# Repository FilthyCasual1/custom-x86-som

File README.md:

# Custom x86 SOM — placement handoff

Open `hardware/x86-som-preliminary.kicad_pro` in KiCad 10. The matching schematic has 18 sheets; the matching PCB contains 96 staged components and zero routed tracks. Project-local symbol and footprint libraries are included. Move components in the PCB editor to start exploring placement; no board outline has been chosen.

**This is an incomplete preliminary design, not fabrication-ready.** See `hardware/LIBRARY-STATUS.md` for the current verification matrix. The CPU socket and Q370 still use padless placement envelopes. Other packages include source-checked geometry and explicitly marked provisional choices. Electrical and assembly validation remains incomplete.

The full library is `hardware/SOM_Full.kicad_sym`; use `hardware/parts-catalog.json` for part numbers. CPU socket: Foxconn PE115127-4041-01H. DDR4 sockets: TE2309407-1. The full pin inventories have1151 CPU contacts,874 PCH balls and456 BMC balls.

## Files

- `hardware/x86-som-preliminary.kicad_sch`: source-based schematic draft.
- `hardware/x86-som-preliminary.kicad_pcb`: component staging board with nets assigned to available pads.
- `hardware/SOM.kicad_sym`, `hardware/SOM.pretty/`: portable project libraries.
- `hardware/footprint-status.json`: footprint provenance and provisional status.
- `hardware/placement-validation.json`: component count and schematic nodes without pads.
- `hardware/open-items.md`: next engineering checks.
- `output/pdf/x86-som-preliminary.pdf`: schematic preview.
- `docs/reference/`, `docs/manifest.json`: downloaded documents and source inventory.
- `research/conversation-source.json`: recovered original specification conversation.

KiCad successfully exported the schematic and reloaded the 96-component PCB. ERC reports 102 errors and 349 warnings; see `hardware/erc.rpt`. These remain unresolved, and no routing, signal-integrity, power-integrity, boot or fabrication validation has been claimed.

The source specification is ChatGPT conversation “Compact SOM Motherboard Design”, ID `6ab03890-806c-83ea-97a4-768561390f3c`. Prior assistant claims are research leads. The earlier claimed downloadable engineering packs were not recovered. Actual donor schematics and manufacturer documents have been downloaded separately.

Generation scripts are development tools. **Do not rerun them after manual KiCad edits:** they overwrite schematic/PCB files and regenerate symbol UUIDs.

## Public repository contents

This public snapshot contains the KiCad files, libraries, generation scripts, engineering notes and previews from local commit `4b89cf6`. The original conversation archive and downloaded third-party reference documents/text extracts remain local; paths to those files describe the local research workspace. `docs/manifest.json` records the source inventory. Some generators require those local source files and will not run from this public checkout alone.

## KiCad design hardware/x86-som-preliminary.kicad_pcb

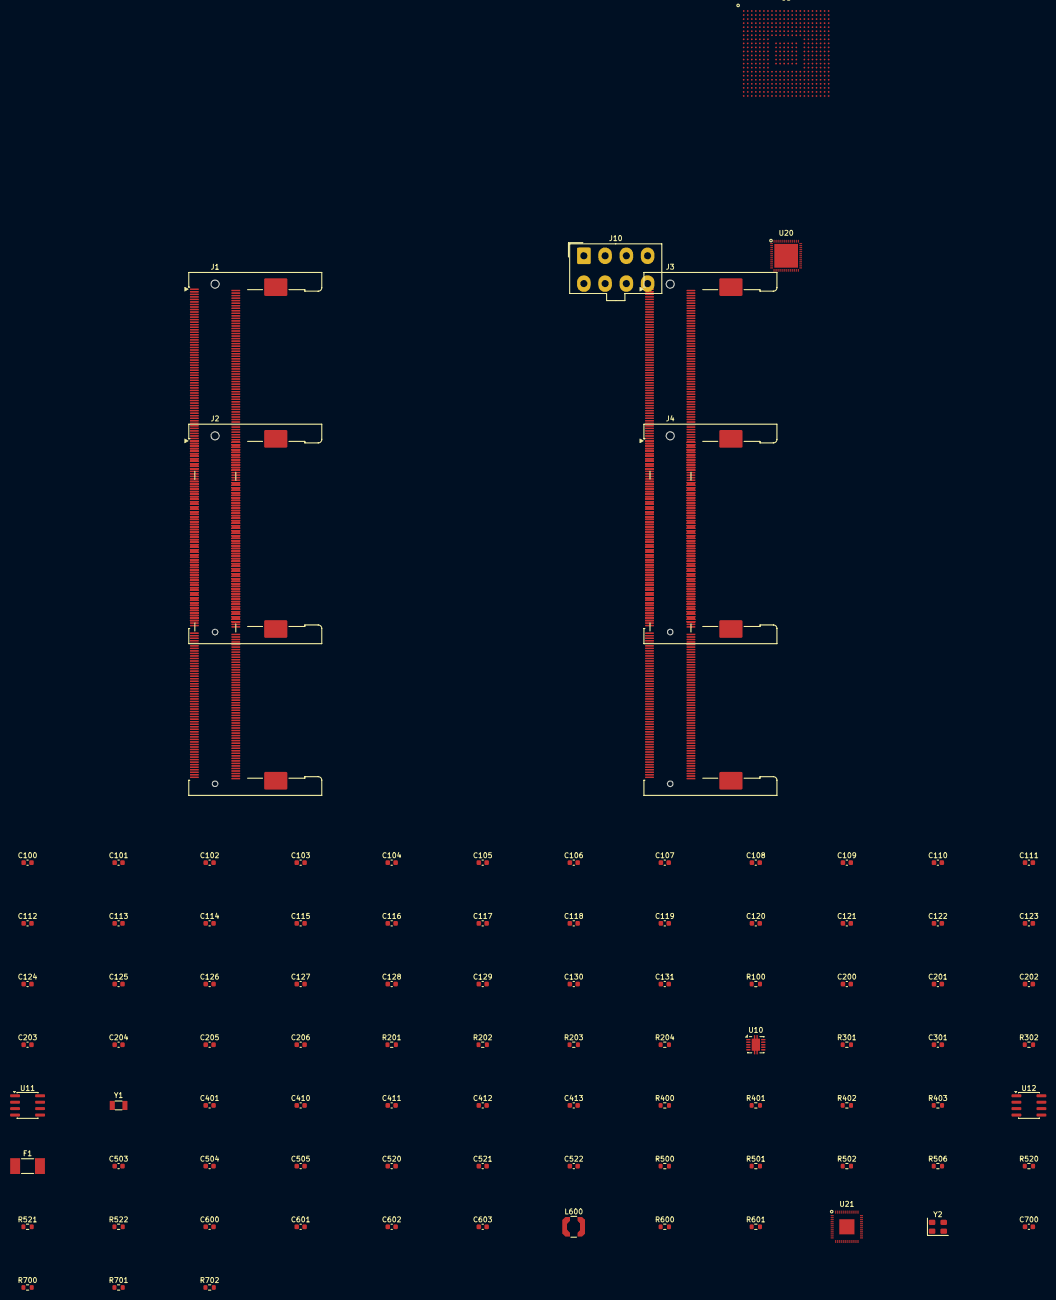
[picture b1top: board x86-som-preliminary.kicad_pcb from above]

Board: 2 copper layers, 96 parts (0 on the bottom side), 267 nets, no tracks yet.

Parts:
C100, C101, C102, C103, C104, C105, C106, C107, C108, C109, C110, C111, C112, C113, C114, C115, C116, C117, C118, C119, C120, C121, C122, C123, C124, C125, C126, C127, C128, C129, C130, C131, C410, C411, C412, C413, C600, C601, C602, C603: 100nF / provisional; C_0603_1608Metric
C200, C201, C202, C205: 10uF; C_0603_1608Metric
C203, C206, C301, C401, C700: 100nF; C_0603_1608Metric
C204, C503, C504, C505: 1uF; C_0603_1608Metric
C520, C521, C522: 220nF / donor; C_0603_1608Metric
F1: Fuse / rating TBD; Fuse_Littelfuse-NANO2-451_453
J1, J2, J3, J4: 260-pin DDR4 SO-DIMM; SODIMM-260_DDR4_H4.0-5.2_OrientationStd_Socket
J10: EPS12V 8-pin; Molex_Mini-Fit_Jr_5566-08A_2x04_P4.20mm_Vertical
L600: 4.7uH / Intel; L_Coilcraft_LPS4018
R100, R301: 24.9R 1%; R_0603_1608Metric
R201, R202: 2.2k / provisional; R_0603_1608Metric
R203, R204: 10k 0.1%; R_0603_1608Metric
R302, R402, R403: 10k / provisional; R_0603_1608Metric
R400: 200R 1%; R_0603_1608Metric
R401: 10k; R_0603_1608Metric
R500, R501, R502: 2.2R; R_0603_1608Metric
R506: 2.87k 1% / donor; R_0603_1608Metric
R520, R521, R522: 2.2R / donor; R_0603_1608Metric
R600: 3.01k 1%; R_0603_1608Metric
R601: 1k; R_0603_1608Metric
R700: 240R 1%; R_0603_1608Metric
R701, R702: 10k 0.1% / provisional; R_0603_1608Metric
U1: Coffee Lake-S / LGA1151; CoffeeLake_LGA1151_PLACEMENT_ONLY
U2: Intel Q370 / draft pin subset; Q370_draft_PLACEMENT_ONLY
U3: AST2500 host/boot subset; ASPEED_AST2500A2_GP_BGA456_19x19_P0.8
U10: TPS51200DRC; VSON-10-1EP_3x3mm_P0.5mm_EP1.65x2.4mm
U11, U12: SPI NOR / capacity TBD; SOIC-8_3.9x4.9mm_P1.27mm
U20: ISL95866HRZ-T / donor reference; Renesas_L52_6x6A_QFN52_EP4.7
U21: I219-LM / revision TBD; Intel_I219_QFN48_EP3
Y1: 32.768kHz / CL TBD; Crystal_SMD_3215-2Pin_3.2x1.5mm
Y2: ABM8-25.000MHZ-D2Y-T; Crystal_SMD_3225-4Pin_3.2x2.5mm

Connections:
AUX_3V3: C204.1, U10.10
AUX_5V: R500.1, R501.1
BMC_3V3: C401.1, R402.2, R403.2, U12.8
BMC_ENTEST: R401.1, U3.K3
BMC_FLASH_HOLD#: R403.1, U12.7
BMC_FLASH_WP#: R402.1, U12.3
BMC_MIOZ: R700.1, U3.W11
BMC_MVREF: C700.1, R701.2, R702.1, U3.T9
BMC_PEREXT: R400.1, U3.K20
BMC_RX_N: C411.2, U3.M22
BMC_RX_P: C410.2, U3.M21
BMC_SPI_CLK: U3.AA18, U12.6
BMC_SPI_CS#: U3.AB19, U12.1
BMC_SPI_MISO: U3.T18, U12.2
BMC_SPI_MOSI: U3.U17, U12.5
BMC_TX_N: C413.1, U3.L22
BMC_TX_P: C412.1, U3.L21
CPU_VCCIO: R100.2, R301.2
DDR_1V2: C205.1, J1.111, J1.112, J1.117, J1.118, J1.123, J1.124, J1.129, J1.130, J1.135, J1.136, J1.141, J1.142, J1.147, J1.148, J1.153, J1.154, J1.159, J1.160, J1.163, J2.111, J2.112, J2.117, J2.118, J2.123, J2.124, J2.129, J2.130, J2.135, J2.136, J2.141, J2.142, J2.147, J2.148, J2.153, J2.154, J2.159, J2.160, J2.163, J3.111, J3.112, J3.117, J3.118, J3.123, J3.124, J3.129, J3.130, J3.135, J3.136, J3.141, J3.142, J3.147, J3.148, J3.153, J3.154, J3.159, J3.160, J3.163, J4.111, J4.112, J4.117, J4.118, J4.123, J4.124, J4.129, J4.130, J4.135, J4.136, J4.141, J4.142, J4.147, J4.148, J4.153, J4.154, J4.159, J4.160, J4.163, R203.1, U10.2
DDR_A_ACT#: J1.114, J2.114
DDR_A_ALERT#: J1.116, J2.116
DDR_A_A[0]: J1.144, J2.144
DDR_A_A[1]: J1.133, J2.133
DDR_A_A[2]: J1.132, J2.132
DDR_A_A[3]: J1.131, J2.131
DDR_A_A[4]: J1.128, J2.128
DDR_A_A[5]: J1.126, J2.126
DDR_A_A[6]: J1.127, J2.127
DDR_A_A[7]: J1.122, J2.122
DDR_A_A[8]: J1.125, J2.125
DDR_A_A[9]: J1.121, J2.121
DDR_A_A[10]: J1.146, J2.146
DDR_A_A[11]: J1.120, J2.120
DDR_A_A[12]: J1.119, J2.119
DDR_A_A[13]: J1.158, J2.158
DDR_A_A[14]: J1.151, J2.151
DDR_A_A[15]: J1.156, J2.156
DDR_A_A[16]: J1.152, J2.152
DDR_A_BA[0]: J1.150, J2.150
DDR_A_BA[1]: J1.145, J2.145
DDR_A_BG[0]: J1.115, J2.115
DDR_A_BG[1]: J1.113, J2.113
DDR_A_DQSN[0]: J1.11, J2.11
DDR_A_DQSN[1]: J1.32, J2.32
DDR_A_DQSN[2]: J1.53, J2.53
DDR_A_DQSN[3]: J1.74, J2.74
DDR_A_DQSN[4]: J1.177, J2.177
DDR_A_DQSN[5]: J1.198, J2.198
DDR_A_DQSN[6]: J1.219, J2.219
DDR_A_DQSN[7]: J1.240, J2.240
DDR_A_DQSP[0]: J1.13, J2.13
DDR_A_DQSP[1]: J1.34, J2.34
DDR_A_DQSP[2]: J1.55, J2.55
DDR_A_DQSP[3]: J1.76, J2.76
DDR_A_DQSP[4]: J1.179, J2.179
DDR_A_DQSP[5]: J1.200, J2.200
DDR_A_DQSP[6]: J1.221, J2.221
DDR_A_DQSP[7]: J1.242, J2.242
DDR_A_DQ[0]: J1.8, J2.8
DDR_A_DQ[1]: J1.7, J2.7
DDR_A_DQ[2]: J1.20, J2.20
DDR_A_DQ[3]: J1.21, J2.21
DDR_A_DQ[4]: J1.4, J2.4
DDR_A_DQ[5]: J1.3, J2.3
DDR_A_DQ[6]: J1.16, J2.16
DDR_A_DQ[7]: J1.17, J2.17
DDR_A_DQ[8]: J1.28, J2.28
DDR_A_DQ[9]: J1.29, J2.29
DDR_A_DQ[10]: J1.41, J2.41
DDR_A_DQ[11]: J1.42, J2.42
DDR_A_DQ[12]: J1.24, J2.24
DDR_A_DQ[13]: J1.25, J2.25
DDR_A_DQ[14]: J1.38, J2.38
DDR_A_DQ[15]: J1.37, J2.37
DDR_A_DQ[16]: J1.50, J2.50
DDR_A_DQ[17]: J1.49, J2.49
DDR_A_DQ[18]: J1.62, J2.62
DDR_A_DQ[19]: J1.63, J2.63
DDR_A_DQ[20]: J1.46, J2.46
DDR_A_DQ[21]: J1.45, J2.45
DDR_A_DQ[22]: J1.58, J2.58
DDR_A_DQ[23]: J1.59, J2.59
DDR_A_DQ[24]: J1.70, J2.70
DDR_A_DQ[25]: J1.71, J2.71
DDR_A_DQ[26]: J1.83, J2.83
DDR_A_DQ[27]: J1.84, J2.84
DDR_A_DQ[28]: J1.66, J2.66
DDR_A_DQ[29]: J1.67, J2.67
DDR_A_DQ[30]: J1.79, J2.79
DDR_A_DQ[31]: J1.80, J2.80
DDR_A_DQ[32]: J1.174, J2.174
DDR_A_DQ[33]: J1.173, J2.173
DDR_A_DQ[34]: J1.187, J2.187
DDR_A_DQ[35]: J1.186, J2.186
DDR_A_DQ[36]: J1.170, J2.170
DDR_A_DQ[37]: J1.169, J2.169
DDR_A_DQ[38]: J1.183, J2.183
DDR_A_DQ[39]: J1.182, J2.182
DDR_A_DQ[40]: J1.195, J2.195
DDR_A_DQ[41]: J1.194, J2.194
DDR_A_DQ[42]: J1.207, J2.207
DDR_A_DQ[43]: J1.208, J2.208
DDR_A_DQ[44]: J1.191, J2.191
DDR_A_DQ[45]: J1.190, J2.190
DDR_A_DQ[46]: J1.203, J2.203
DDR_A_DQ[47]: J1.204, J2.204
DDR_A_DQ[48]: J1.216, J2.216
DDR_A_DQ[49]: J1.215, J2.215
DDR_A_DQ[50]: J1.228, J2.228
DDR_A_DQ[51]: J1.229, J2.229
DDR_A_DQ[52]: J1.211, J2.211
DDR_A_DQ[53]: J1.212, J2.212
DDR_A_DQ[54]: J1.224, J2.224
DDR_A_DQ[55]: J1.225, J2.225
DDR_A_DQ[56]: J1.237, J2.237
DDR_A_DQ[57]: J1.236, J2.236
DDR_A_DQ[58]: J1.249, J2.249
DDR_A_DQ[59]: J1.250, J2.250
DDR_A_DQ[60]: J1.232, J2.232
DDR_A_DQ[61]: J1.233, J2.233
DDR_A_DQ[62]: J1.245, J2.245
DDR_A_DQ[63]: J1.246, J2.246
DDR_A_EVENT#: J1.134, J2.134
DDR_A_PARITY: J1.143, J2.143
DDR_B_ACT#: J3.114, J4.114
DDR_B_ALERT#: J3.116, J4.116
DDR_B_A[0]: J3.144, J4.144
DDR_B_A[1]: J3.133, J4.133
DDR_B_A[2]: J3.132, J4.132
DDR_B_A[3]: J3.131, J4.131
DDR_B_A[4]: J3.128, J4.128
DDR_B_A[5]: J3.126, J4.126
DDR_B_A[6]: J3.127, J4.127
DDR_B_A[7]: J3.122, J4.122
DDR_B_A[8]: J3.125, J4.125
DDR_B_A[9]: J3.121, J4.121
DDR_B_A[10]: J3.146, J4.146
DDR_B_A[11]: J3.120, J4.120
DDR_B_A[12]: J3.119, J4.119
DDR_B_A[13]: J3.158, J4.158
DDR_B_A[14]: J3.151, J4.151
DDR_B_A[15]: J3.156, J4.156
DDR_B_A[16]: J3.152, J4.152
DDR_B_BA[0]: J3.150, J4.150
DDR_B_BA[1]: J3.145, J4.145
DDR_B_BG[0]: J3.115, J4.115
DDR_B_BG[1]: J3.113, J4.113
DDR_B_DQSN[0]: J3.11, J4.11
DDR_B_DQSN[1]: J3.32, J4.32
DDR_B_DQSN[2]: J3.53, J4.53
DDR_B_DQSN[3]: J3.74, J4.74
DDR_B_DQSN[4]: J3.177, J4.177
DDR_B_DQSN[5]: J3.198, J4.198
DDR_B_DQSN[6]: J3.219, J4.219
DDR_B_DQSN[7]: J3.240, J4.240
DDR_B_DQSP[0]: J3.13, J4.13
DDR_B_DQSP[1]: J3.34, J4.34
DDR_B_DQSP[2]: J3.55, J4.55
DDR_B_DQSP[3]: J3.76, J4.76
DDR_B_DQSP[4]: J3.179, J4.179
DDR_B_DQSP[5]: J3.200, J4.200
DDR_B_DQSP[6]: J3.221, J4.221
DDR_B_DQSP[7]: J3.242, J4.242
DDR_B_DQ[0]: J3.8, J4.8
DDR_B_DQ[1]: J3.7, J4.7
DDR_B_DQ[2]: J3.20, J4.20
DDR_B_DQ[3]: J3.21, J4.21
DDR_B_DQ[4]: J3.4, J4.4
DDR_B_DQ[5]: J3.3, J4.3
DDR_B_DQ[6]: J3.16, J4.16
DDR_B_DQ[7]: J3.17, J4.17
DDR_B_DQ[8]: J3.28, J4.28
DDR_B_DQ[9]: J3.29, J4.29
DDR_B_DQ[10]: J3.41, J4.41
DDR_B_DQ[11]: J3.42, J4.42
DDR_B_DQ[12]: J3.24, J4.24
DDR_B_DQ[13]: J3.25, J4.25
DDR_B_DQ[14]: J3.38, J4.38
DDR_B_DQ[15]: J3.37, J4.37
DDR_B_DQ[16]: J3.50, J4.50
DDR_B_DQ[17]: J3.49, J4.49
DDR_B_DQ[18]: J3.62, J4.62
DDR_B_DQ[19]: J3.63, J4.63
DDR_B_DQ[20]: J3.46, J4.46
DDR_B_DQ[21]: J3.45, J4.45
DDR_B_DQ[22]: J3.58, J4.58
DDR_B_DQ[23]: J3.59, J4.59
DDR_B_DQ[24]: J3.70, J4.70
DDR_B_DQ[25]: J3.71, J4.71
DDR_B_DQ[26]: J3.83, J4.83
DDR_B_DQ[27]: J3.84, J4.84
DDR_B_DQ[28]: J3.66, J4.66
DDR_B_DQ[29]: J3.67, J4.67
DDR_B_DQ[30]: J3.79, J4.79
DDR_B_DQ[31]: J3.80, J4.80
DDR_B_DQ[32]: J3.174, J4.174
DDR_B_DQ[33]: J3.173, J4.173
DDR_B_DQ[34]: J3.187, J4.187
DDR_B_DQ[35]: J3.186, J4.186
DDR_B_DQ[36]: J3.170, J4.170
DDR_B_DQ[37]: J3.169, J4.169
DDR_B_DQ[38]: J3.183, J4.183
DDR_B_DQ[39]: J3.182, J4.182
DDR_B_DQ[40]: J3.195, J4.195
DDR_B_DQ[41]: J3.194, J4.194
DDR_B_DQ[42]: J3.207, J4.207
DDR_B_DQ[43]: J3.208, J4.208
DDR_B_DQ[44]: J3.191, J4.191
DDR_B_DQ[45]: J3.190, J4.190
DDR_B_DQ[46]: J3.203, J4.203
DDR_B_DQ[47]: J3.204, J4.204
DDR_B_DQ[48]: J3.216, J4.216
DDR_B_DQ[49]: J3.215, J4.215
DDR_B_DQ[50]: J3.228, J4.228
DDR_B_DQ[51]: J3.229, J4.229
DDR_B_DQ[52]: J3.211, J4.211
DDR_B_DQ[53]: J3.212, J4.212
DDR_B_DQ[54]: J3.224, J4.224
DDR_B_DQ[55]: J3.225, J4.225
DDR_B_DQ[56]: J3.237, J4.237
DDR_B_DQ[57]: J3.236, J4.236
DDR_B_DQ[58]: J3.249, J4.249
DDR_B_DQ[59]: J3.250, J4.250
DDR_B_DQ[60]: J3.232, J4.232
DDR_B_DQ[61]: J3.233, J4.233
DDR_B_DQ[62]: J3.245, J4.245
DDR_B_DQ[63]: J3.246, J4.246
DDR_B_EVENT#: J3.134, J4.134
DDR_B_PARITY: J3.143, J4.143
DDR_REFIN_0V6: C206.1, R203.2, R204.1, U10.1
DDR_RESET#: J1.108, J2.108, J3.108, J4.108
DDR_VPP_2V5: J1.257, J1.259, J2.257, J2.259, J3.257, J3.259, J4.257, J4.259
DDR_VREFCA: C203.1, J1.164, J2.164, J3.164, J4.164, U10.6
DDR_VTT: C200.1, C201.1, C202.1, J1.258, J2.258, J3.258, J4.258, U10.3, U10.5
EPS_12V: F1.1, J10.5, J10.6, J10.7, J10.8
GND: C200.2, C201.2, C202.2, C203.2, C204.2, C205.2, C206.2, C301.2, C401.2, C503.2, C504.2, C505.2, C700.2, J1.1, J1.2, J1.5, J1.6, J1.9, J1.10, J1.14, J1.15, J1.18, J1.19, J1.22, J1.23, J1.26, J1.27, J1.30, J1.31, J1.35, J1.36, J1.39, J1.40, J1.43, J1.44, J1.47, J1.48, J1.51, J1.52, J1.56, J1.57, J1.60, J1.61, J1.64, J1.65, J1.68, J1.69, J1.72, J1.73, J1.77, J1.78, J1.81, J1.82, J1.85, J1.86, J1.89, J1.90, J1.93, J1.94, J1.98, J1.99, J1.102, J1.103, J1.106, J1.107, J1.166, J1.167, J1.168, J1.171, J1.172, J1.175, J1.176, J1.180, J1.181, J1.184, J1.185, J1.188, J1.189, J1.192, J1.193, J1.196, J1.197, J1.201, J1.202, J1.205, J1.206, J1.209, J1.210, J1.213, J1.214, J1.217, J1.218, J1.222, J1.223, J1.226, J1.227, J1.230, J1.231, J1.234, J1.235, J1.238, J1.239, J1.243, J1.244, J1.247, J1.248, J1.251, J1.252, J1.256, J1.260, J2.1, J2.2, J2.5, J2.6, J2.9, J2.10, J2.14, J2.15, J2.18, J2.19, J2.22, J2.23, J2.26, J2.27, J2.30, J2.31, J2.35, J2.36, J2.39, J2.40, J2.43, J2.44, J2.47, J2.48, J2.51, J2.52, J2.56, J2.57, J2.60, J2.61, J2.64, J2.65, J2.68, J2.69, J2.72, J2.73, J2.77, J2.78, J2.81, J2.82, J2.85, J2.86, J2.89, J2.90, J2.93, J2.94, J2.98, J2.99, J2.102, J2.103, J2.106, J2.107, J2.166, J2.167, J2.168, J2.171, J2.172, J2.175, J2.176, J2.180, J2.181, J2.184, J2.185, J2.188, J2.189, J2.192, J2.193, J2.196, J2.197, J2.201, J2.202, J2.205, J2.206, J2.209, J2.210, J2.213, J2.214, J2.217, J2.218, J2.222, J2.223, J2.226, J2.227, J2.230, J2.231, J2.234, J2.235, J2.238, J2.239, J2.243, J2.244, J2.247, J2.248, J2.251, J2.252, J2.260, J3.1, J3.2, J3.5, J3.6, J3.9, J3.10, J3.14, J3.15, J3.18, J3.19, J3.22, J3.23, J3.26, J3.27, J3.30, J3.31, J3.35, J3.36, J3.39, J3.40, J3.43, J3.44, J3.47, J3.48, J3.51, J3.52, J3.56, J3.57, J3.60, J3.61, J3.64, J3.65, J3.68, J3.69, J3.72, J3.73, J3.77, J3.78, J3.81, J3.82, J3.85, J3.86, J3.89, J3.90, J3.93, J3.94, J3.98, J3.99, J3.102, J3.103, J3.106, J3.107, J3.166, J3.167, J3.168, J3.171, J3.172, J3.175, J3.176, J3.180, J3.181, J3.184, J3.185, J3.188, J3.189, J3.192, J3.193, J3.196, J3.197, J3.201, J3.202, J3.205, J3.206, J3.209, J3.210, J3.213, J3.214, J3.217, J3.218, J3.222, J3.223, J3.226, J3.227, J3.230, J3.231, J3.234, J3.235, J3.238, J3.239, J3.243, J3.244, J3.247, J3.248, J3.251, J3.252, J3.256, J4.1, J4.2, J4.5, J4.6, J4.9, J4.10, J4.14, J4.15, J4.18, J4.19, J4.22, J4.23, J4.26, J4.27, J4.30, J4.31, J4.35, J4.36, J4.39, J4.40, J4.43, J4.44, J4.47, J4.48, J4.51, J4.52, J4.56, J4.57, J4.60, J4.61, J4.64, J4.65, J4.68, J4.69, J4.72, J4.73, J4.77, J4.78, J4.81, J4.82, J4.85, J4.86, J4.89, J4.90, J4.93, J4.94, J4.98, J4.99, J4.102, J4.103, J4.106, J4.107, J4.166, J4.167, J4.168, J4.171, J4.172, J4.175, J4.176, J4.180, J4.181, J4.184, J4.185, J4.188, J4.189, J4.192, J4.193, J4.196, J4.197, J4.201, J4.202, J4.205, J4.206, J4.209, J4.210, J4.213, J4.214, J4.217, J4.218, J4.222, J4.223, J4.226, J4.227, J4.230, J4.231, J4.234, J4.235, J4.238, J4.239, J4.243, J4.244, J4.247, J4.248, J4.251, J4.252, J10.1, J10.2, J10.3, J10.4, R204.2, R400.2, R401.2, R506.2, R600.2, R601.2, R700.2, R702.2, U10.4, U10.8, U10.11, U11.4, U12.4, U20.53, U21.6, U21.49, Y2.2, Y2.4
HOST_SPI_CS#: R302.1, U11.1
HOST_VDD0P9: L600.2, U21.8, U21.11, U21.16, U21.22, U21.37, U21.40, U21.43, U21.46, U21.47
HOST_VDD3P3: U21.4, U21.15, U21.19, U21.29
HOST_XTAL_IN: U21.10, Y2.3
HOST_XTAL_OUT: U21.9, Y2.1
I219_RBIAS: R600.1, U21.12
I219_RX_N: C601.2, U21.42
I219_RX_P: C600.2, U21.41
I219_SW_0V9: L600.1, U21.7
I219_TEST_EN: R601.1, U21.30
I219_TX_N: C603.1, U21.39
I219_TX_P: C602.1, U21.38
PCH_VCCSPI: C301.1, R302.2, U11.8
PLTRST#: U3.G22, U3.L20, U21.36
SMBCLK: J1.253, J2.253, J3.253, J4.253, R201.1, U20.42
SMBDATA: J1.254, J2.254, J3.254, J4.254, R202.1, U20.43
SPD_3V3: J1.255, J2.255, J2.256, J3.255, J3.260, J4.255, J4.256, J4.260, R201.2, R202.2
VIN_12V_PROTECTED: F1.2, R502.1
VR_BOOT1_A: R520.1, U20.25
VR_BOOT1_A_CAP: C520.1, R520.2
VR_BOOT1_B: R522.1, U20.37
VR_BOOT1_B_CAP: C522.1, R522.2
VR_BOOT2_A: R521.1, U20.29
VR_BOOT2_A_CAP: C521.1, R521.2
VR_PHASE1_A: C520.2, U20.26
VR_PHASE1_B: C522.2, U20.35
VR_PHASE2_A: C521.2, U20.30
VR_PROG: R506.1, U20.10
VR_VDDP_5V: C504.1, R501.2, U20.32
VR_VDD_5V: C503.1, R500.2, U20.24
VR_VIN: C505.1, R502.2, U20.44

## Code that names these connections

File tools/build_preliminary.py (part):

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 if b in pb: pch_boot.append(pin(b,n))
# SMB pins corrected below from table, not assumed generic GPIO numbers.
for p in pch_boot:
 if p['name']=='SMBCLK':p['pin']='BE26'
 if p['name']=='SMBDATA':p['pin']='BF26'
pch_io=[p for p in pch if re.fullmatch(r'USB2[NP]_\d+',p['name'])]+[p for p in pch if re.fullmatch(r'CLKOUT_PCIE_[NP]\d+',p['name'])]
pch_power=[dict(p,stack=p['name'],type='power_in') for p in pch if p['name'].startswith(('VCC','VSS','DCPRTC'))]
# Do not conflate sense and internally generated supplies with external outputs.
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for i in range(16):
 for j,pol in enumerate('PN'):
  k=2*i+j;s.part('C',f'C{100+k}','100nF / provisional',310+(k//16)*130,65+(k%16)*15,f'PEG_TX_{i}{pol}',f'CARRIER_PEG_TX_{i}{pol}')
s.part('R','R100','24.9R 1%',100,225,'CPU_PEG_COMP','CPU_VCCIO');s.text('CFG[6:5] = 10 for 2x8. Physical strap aliases still require verification; do not guess pin mapping.',20,360,1.3)
for ch,unit in [('A',3),('B',4)]:
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 s.symbol('CoffeeLake_LGA1151','U1',92,60,cpu_nets,unit)
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 s.text('No ECC. Address/command termination and per-socket decoupling are not yet sized. SPD addresses 0x50-0x53.',20,385,1.2)
s=Sheet('05_memory_power','DDR4 supply interfaces, termination and socket power',['DDR_1V2 and DDR_VPP_2V5 regulators remain to size for four modules. VTT circuit follows TPS51200.','Shown capacitors are preliminary, not a complete PDN. Memory VREF_DQ handling still needs CPU guidance.'])
for i in range(4):
 nets={p['pin']:('GND'if p['name'].startswith('VSS')else'SPD_3V3'if p['name']=='VDDSPD'else'DDR_VPP_2V5'if p['name'].startswith('VPP')else'DDR_VTT'if p['name']=='VTT'else'DDR_VREFCA'if p['name']=='VREFCA'else'DDR_1V2')for p in dp}
 s.symbol('DDR4_SODIMM_260',f'J{i+1}',90+i*135,60,nets,2)
s.symbol('TPS51200','U10',115,135,{'1':'DDR_REFIN_0V6','2':'DDR_1V2','3':'DDR_VTT','4':'GND','5':'DDR_VTT','6':'DDR_VREFCA','7':'DDR_VTT_EN','8':'GND','9':'DDR_VTT_PGOOD','10':'AUX_3V3','11':'GND'})
for idx,(a,b,val) in enumerate([('DDR_VTT','GND','10uF'),('DDR_VTT','GND','10uF'),('DDR_VTT','GND','10uF'),('DDR_VREFCA','GND','100nF'),('AUX_3V3','GND','1uF'),('DDR_1V2','GND','10uF')]):s.part('C',f'C{200+idx}',val,300+(idx//3)*130,145+(idx%3)*30,a,b)
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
